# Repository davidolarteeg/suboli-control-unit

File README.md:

SUBOLI MK2 control unit — KiCad 10 project for design review.

Current procurement and missing-component tracker: `procurement/INVENTORY.md`.

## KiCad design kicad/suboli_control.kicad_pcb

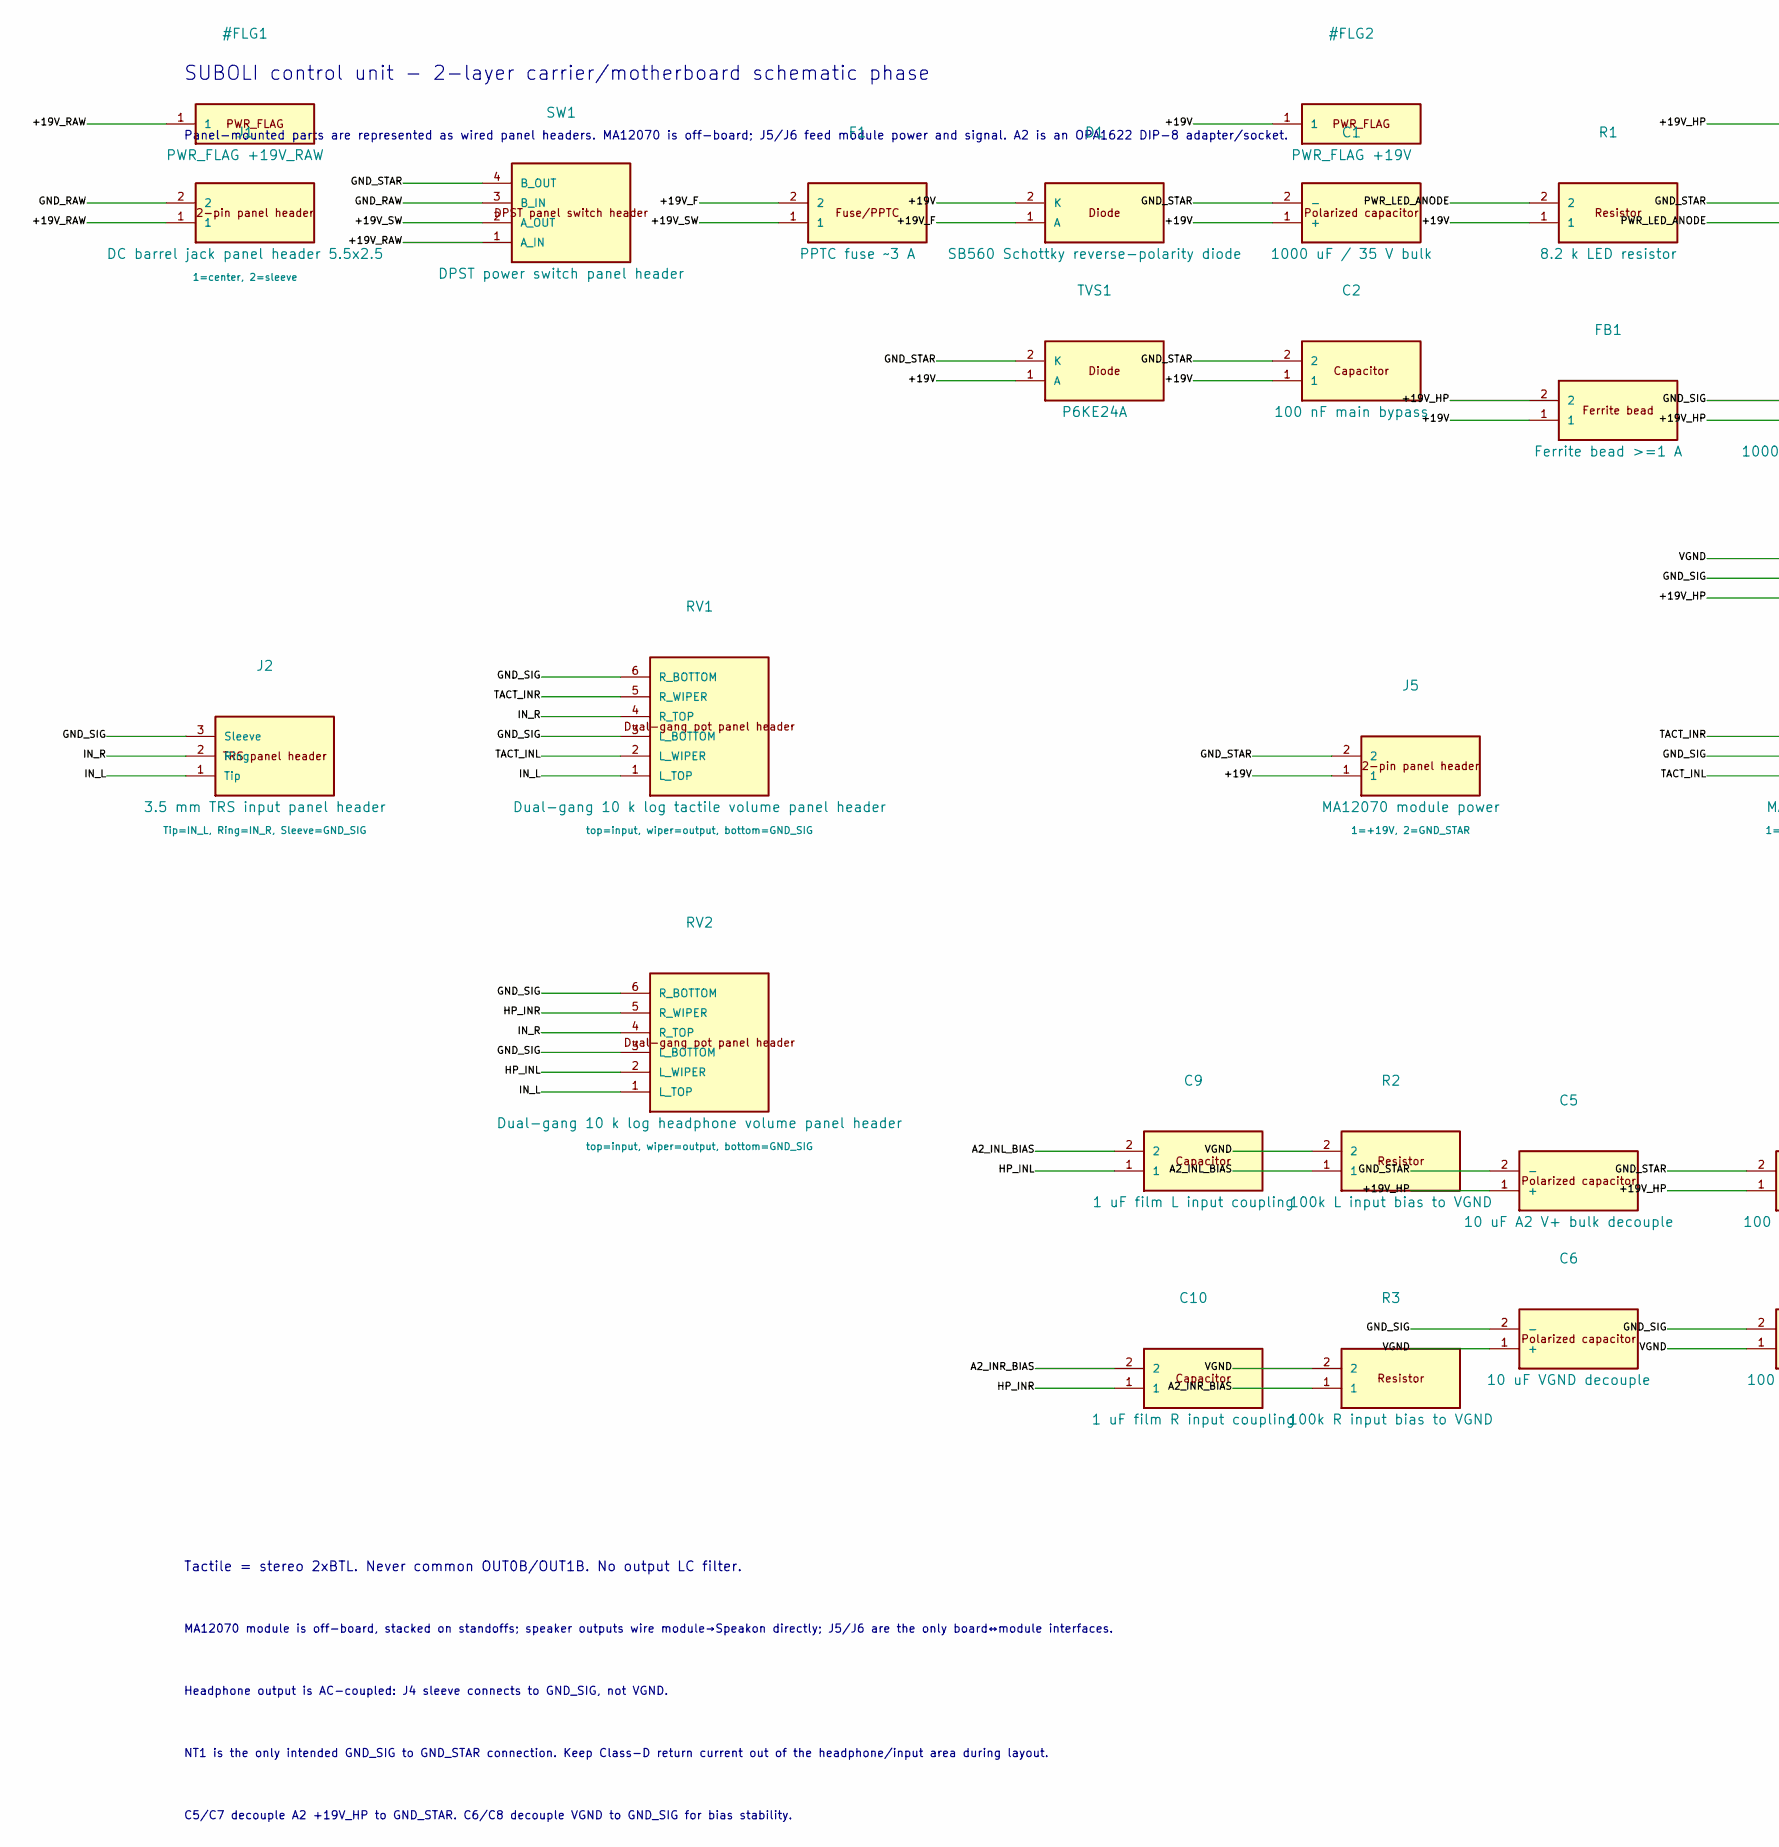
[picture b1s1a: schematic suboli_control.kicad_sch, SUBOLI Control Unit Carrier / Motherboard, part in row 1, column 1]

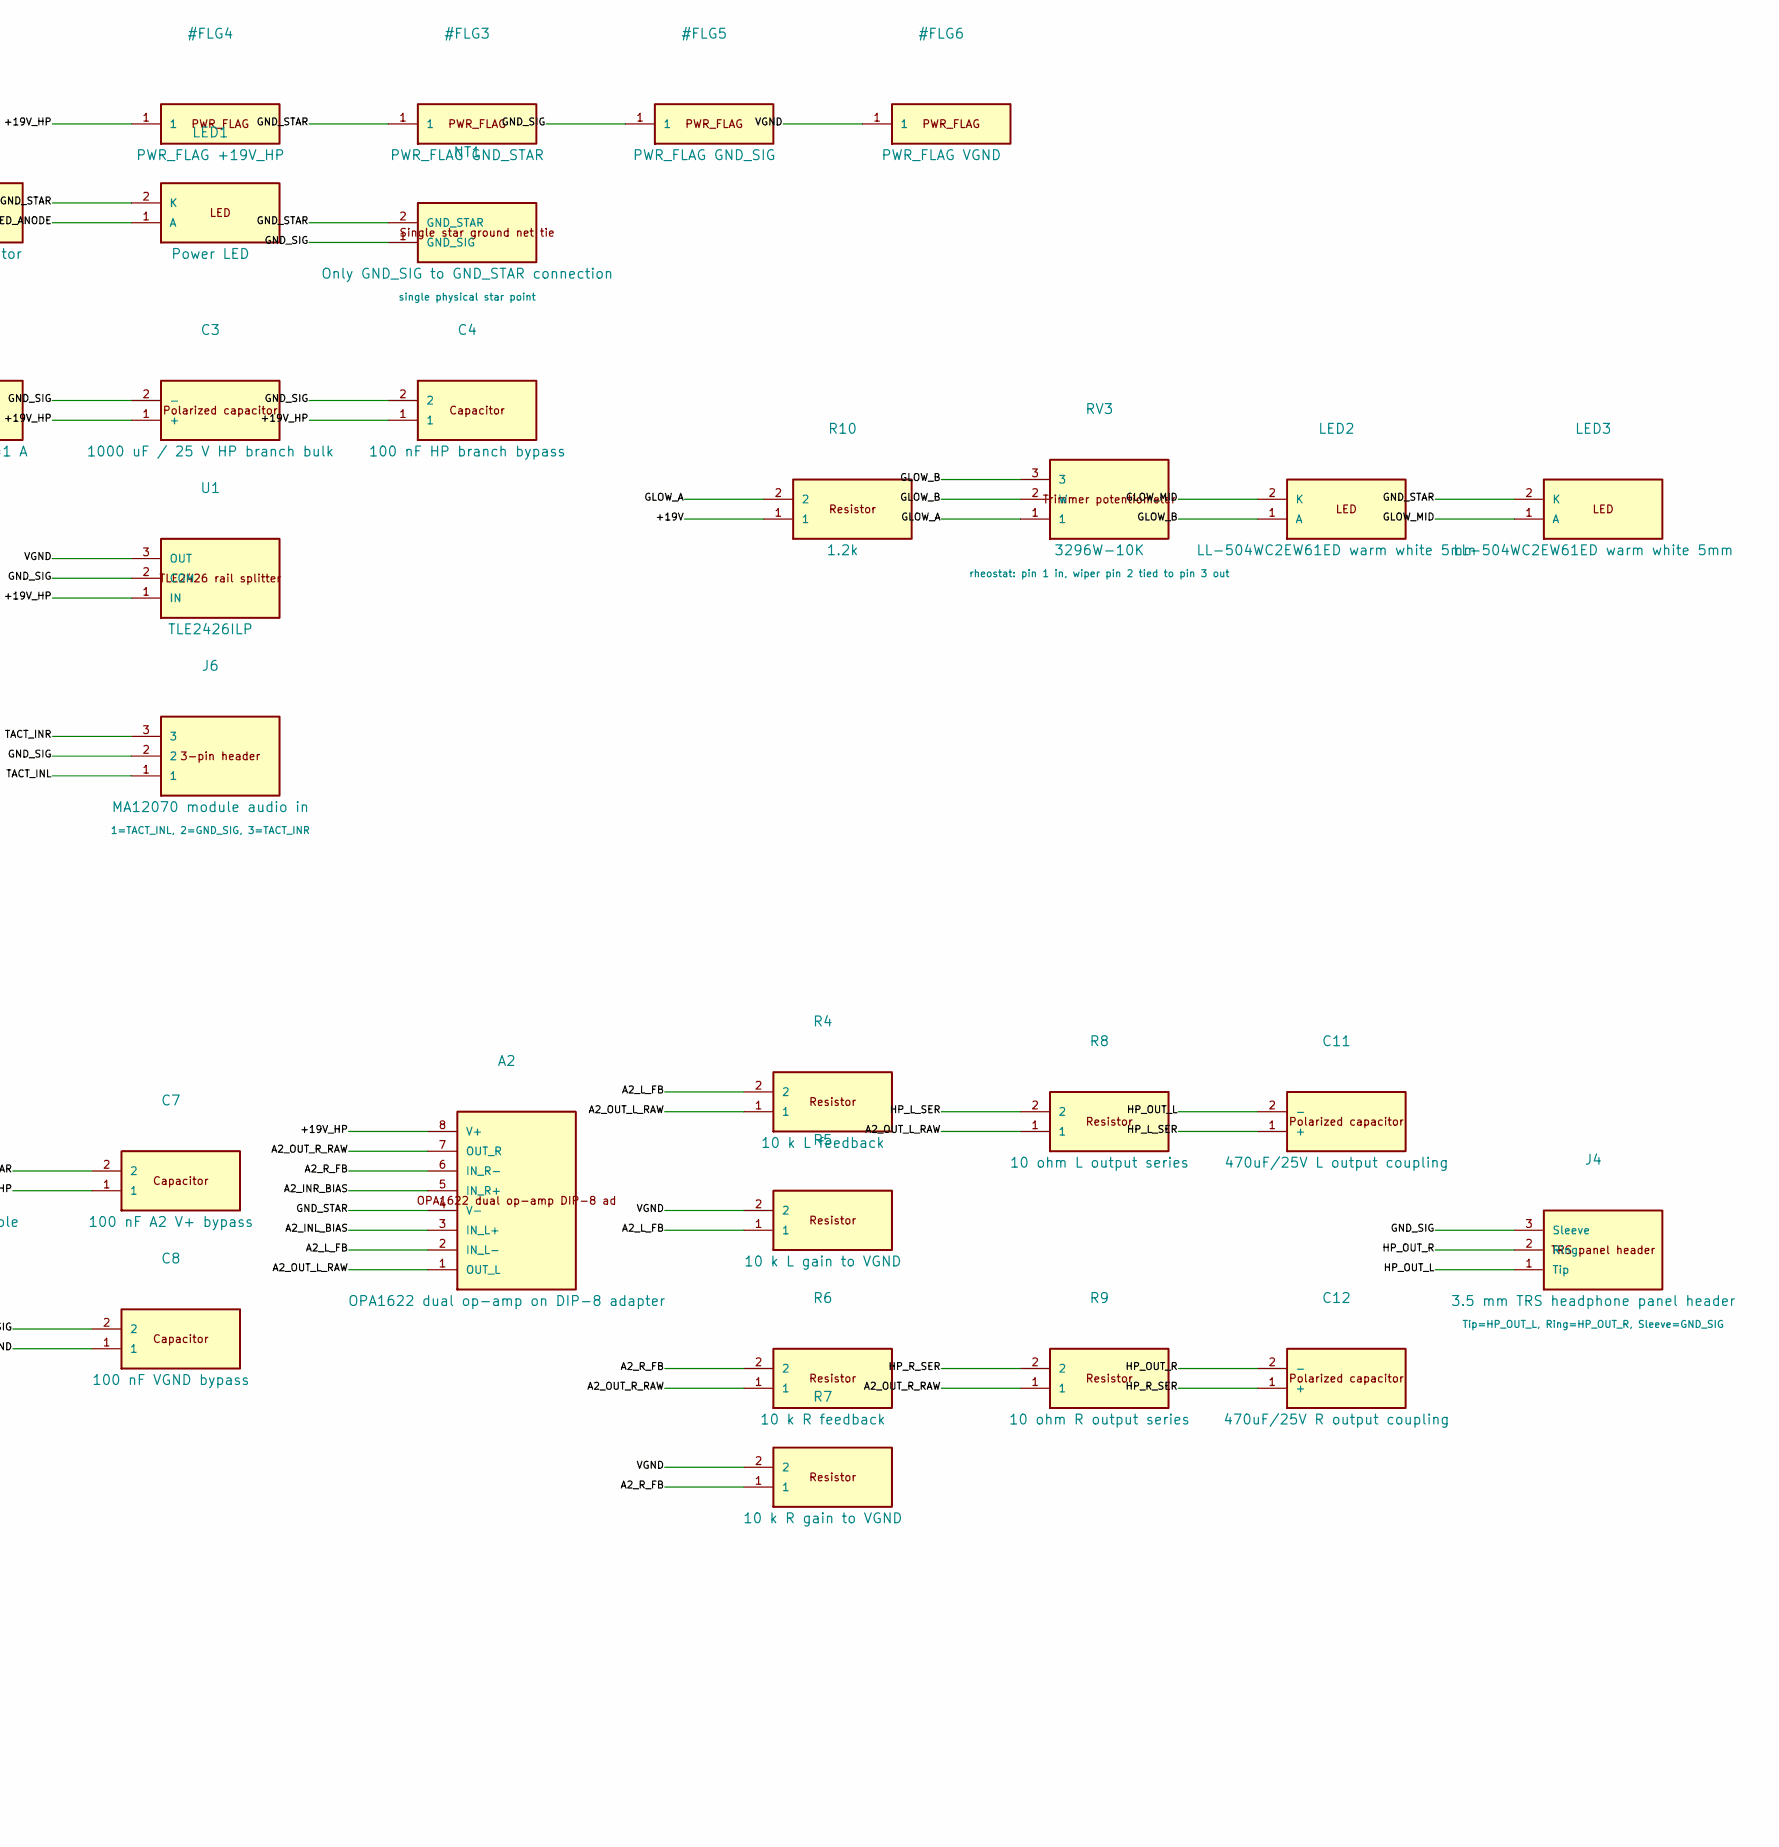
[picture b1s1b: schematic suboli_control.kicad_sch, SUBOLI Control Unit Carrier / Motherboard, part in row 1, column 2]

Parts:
A2: OPA1622 dual op-amp on DIP-8 adapter; DIP-8_W7.62mm_Socket
C1: 1000 uF / 35 V bulk; CP_Radial_D16.0mm_P7.50mm
C2: 100 nF main bypass; C_Disc_D7.5mm_W4.4mm_P5.00mm
C3: 1000 uF / 25 V HP branch bulk; CP_Radial_D10.0mm_P5.00mm
C4: 100 nF HP branch bypass; C_Disc_D7.5mm_W4.4mm_P5.00mm
C5: 10 uF A2 V+ bulk decouple; CP_Radial_D5.0mm_P2.00mm
C6: 10 uF VGND decouple; CP_Radial_D5.0mm_P2.00mm
C7: 100 nF A2 V+ bypass; C_Disc_D7.5mm_W4.4mm_P5.00mm
C8: 100 nF VGND bypass; C_Disc_D7.5mm_W4.4mm_P5.00mm
C9: 1 uF film L input coupling; C_Rect_L7.2mm_W4.5mm_P5.00mm
C10: 1 uF film R input coupling; C_Rect_L7.2mm_W4.5mm_P5.00mm
C11: 470uF/25V L output coupling; CP_Radial_D10.0mm_P5.00mm
C12: 470uF/25V R output coupling; CP_Radial_D10.0mm_P5.00mm
D1: SB560 Schottky reverse-polarity diode; D_DO-201AD_P15.24mm_Horizontal
F1: PPTC fuse ~3 A; PPTC_LP30-300_P7.60mm
FB1: Ferrite bead >=1 A; L_Axial_L12.0mm_D5.0mm_P15.24mm_Horizontal_Fastron_MISC
J1: DC barrel jack panel header 5.5x2.5; PhoenixContact_MSTBA_2,5_2-G-5,08_1x02_P5.08mm_Horizontal
J2: 3.5 mm TRS input panel header; JST_XH_B3B-XH-A_1x03_P2.50mm_Vertical
J4: 3.5 mm TRS headphone panel header; JST_XH_B3B-XH-A_1x03_P2.50mm_Vertical
J5: MA12070 module power; PhoenixContact_MSTBA_2,5_2-G-5,08_1x02_P5.08mm_Horizontal
J6: MA12070 module audio in; JST_XH_B3B-XH-A_1x03_P2.50mm_Vertical
LED1: Power LED; LED_D5.0mm
LED2, LED3: LL-504WC2EW61ED warm white 5mm; LED_D5.0mm
NT1: Only GND_SIG to GND_STAR connection; NetTie-2_SMD_Pad0.5mm
R1: 8.2 k LED resistor; R_Axial_DIN0207_L6.3mm_D2.5mm_P10.16mm_Horizontal
R2: 100k L input bias to VGND; R_Axial_DIN0207_L6.3mm_D2.5mm_P10.16mm_Horizontal
R3: 100k R input bias to VGND; R_Axial_DIN0207_L6.3mm_D2.5mm_P10.16mm_Horizontal
R4: 10 k L feedback; R_Axial_DIN0207_L6.3mm_D2.5mm_P10.16mm_Horizontal
R5: 10 k L gain to VGND; R_Axial_DIN0207_L6.3mm_D2.5mm_P10.16mm_Horizontal
R6: 10 k R feedback; R_Axial_DIN0207_L6.3mm_D2.5mm_P10.16mm_Horizontal
R7: 10 k R gain to VGND; R_Axial_DIN0207_L6.3mm_D2.5mm_P10.16mm_Horizontal
R8: 10 ohm L output series; R_Axial_DIN0207_L6.3mm_D2.5mm_P10.16mm_Horizontal
R9: 10 ohm R output series; R_Axial_DIN0207_L6.3mm_D2.5mm_P10.16mm_Horizontal
R10: 1.2k; R_Axial_DIN0207_L6.3mm_D2.5mm_P10.16mm_Horizontal
RV1: Dual-gang 10 k log tactile volume panel header; JST_XH_B6B-XH-A_1x06_P2.50mm_Vertical
RV2: Dual-gang 10 k log headphone volume panel header; JST_XH_B6B-XH-A_1x06_P2.50mm_Vertical
RV3: 3296W-10K; Potentiometer_Bourns_3296W_Vertical
SW1: DPST power switch panel header; PhoenixContact_MSTBA_2,5_4-G-5,08_1x04_P5.08mm_Horizontal
TVS1: P6KE24A; D_DO-15_P10.16mm_Horizontal
U1: TLE2426ILP; TO-92_Inline

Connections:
/+19V: C1.1 (+), C2.1, D1.2 (K), FB1.1, J5.1, R1.1, R10.1, TVS1.1 (A)
/+19V_F: D1.1 (A), F1.2
/+19V_HP: A2.8 (V+), C3.1 (+), C4.1, C5.1 (+), C7.1, FB1.2, U1.1 (IN)
/+19V_RAW: J1.1, SW1.1 (A_IN)
/+19V_SW: F1.1, SW1.2 (A_OUT)
/A2_INL_BIAS: A2.3 (IN_L+), C9.2, R2.1
/A2_INR_BIAS: A2.5 (IN_R+), C10.2, R3.1
/A2_L_FB: A2.2 (IN_L-), R4.2, R5.1
/A2_OUT_L_RAW: A2.1 (OUT_L), R4.1, R8.1
/A2_OUT_R_RAW: A2.7 (OUT_R), R6.1, R9.1
/A2_R_FB: A2.6 (IN_R-), R6.2, R7.1
/GLOW_A: R10.2, RV3.1
/GLOW_B: LED2.1 (A), RV3.2 (W), RV3.3
/GLOW_MID: LED2.2 (K), LED3.1 (A)
/GND_RAW: J1.2, SW1.3 (B_IN)
/GND_SIG: C3.2 (-), C4.2, C6.2 (-), C8.2, J2.3 (Sleeve), J4.3 (Sleeve), J6.2, NT1.1 (GND_SIG), RV1.3 (L_BOTTOM), RV1.6 (R_BOTTOM), RV2.3 (L_BOTTOM), RV2.6 (R_BOTTOM), U1.2 (COM)
/GND_STAR: A2.4 (V-), C1.2 (-), C2.2, C5.2 (-), C7.2, J5.2, LED1.2 (K), LED3.2 (K), NT1.2 (GND_STAR), SW1.4 (B_OUT), TVS1.2 (K)
/HP_INL: C9.1, RV2.2 (L_WIPER)
/HP_INR: C10.1, RV2.5 (R_WIPER)
/HP_L_SER: C11.1 (+), R8.2
/HP_OUT_L: C11.2 (-), J4.1 (Tip)
/HP_OUT_R: C12.2 (-), J4.2 (Ring)
/HP_R_SER: C12.1 (+), R9.2
/IN_L: J2.1 (Tip), RV1.1 (L_TOP), RV2.1 (L_TOP)
/IN_R: J2.2 (Ring), RV1.4 (R_TOP), RV2.4 (R_TOP)
/PWR_LED_ANODE: LED1.1 (A), R1.2
/TACT_INL: J6.1, RV1.2 (L_WIPER)
/TACT_INR: J6.3, RV1.5 (R_WIPER)
/VGND: C6.1 (+), C8.1, R2.2, R3.2, R5.2, R7.2, U1.3 (OUT)

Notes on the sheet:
SUBOLI control unit - 2-layer carrier/motherboard schematic phase
Panel-mounted parts are represented as wired panel headers. MA12070 is off-board; J5/J6 feed module power and signal. A2 is an OPA1622 DIP-8 adapter/socket.
Tactile = stereo 2xBTL. Never common OUT0B/OUT1B. No output LC filter.
MA12070 module is off-board, stacked on standoffs; speaker outputs wire module→Speakon directly; J5/J6 are the only board↔module interfaces.
Headphone output is AC-coupled: J4 sleeve connects to GND_SIG, not VGND.
NT1 is the only intended GND_SIG to GND_STAR connection. Keep Class-D return current out of the headphone/input area during layout.
C5/C7 decouple A2 +19V_HP to GND_STAR. C6/C8 decouple VGND to GND_SIG for bias stability.

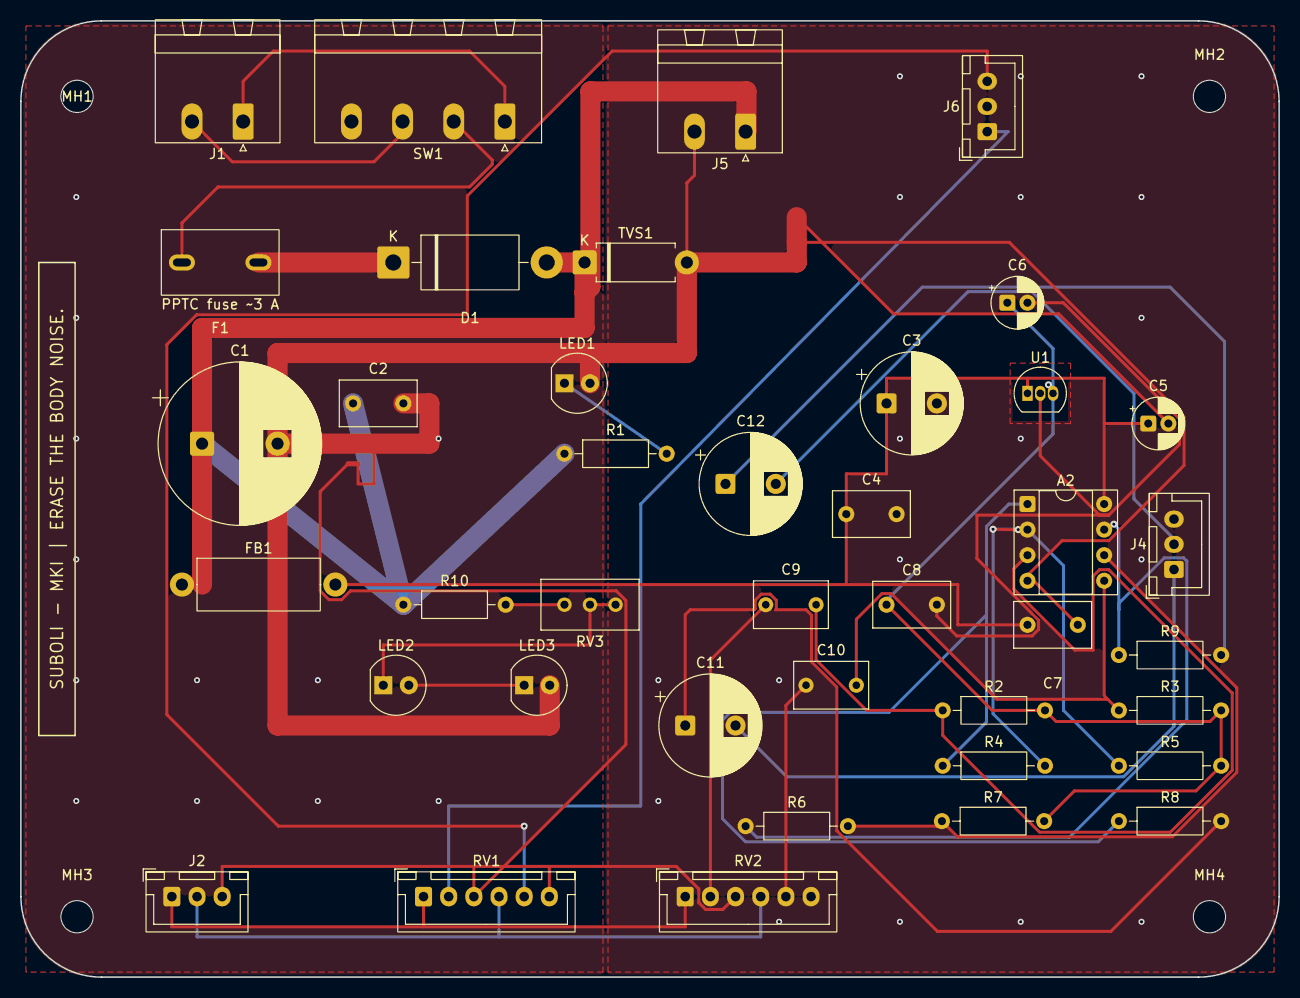
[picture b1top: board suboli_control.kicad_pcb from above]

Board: 2 copper layers, 125.0 x 95.0 mm, 45 parts (0 on the bottom side), 29 nets.

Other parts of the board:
MH1, MH2, MH3, MH4: MountingHole_3.2mm_M3

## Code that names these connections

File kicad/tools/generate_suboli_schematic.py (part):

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    Component("TVS1", "SMBJ20A TVS", "D_2PIN", 138, 54, {"1": "+19V", "2": "GND_STAR"}),
    Component("C1", "1000 uF / 35 V bulk", "CP_2PIN", 170, 34, {"1": "+19V", "2": "GND_STAR"}),
    Component("C2", "100 nF main bypass", "C_2PIN", 170, 54, {"1": "+19V", "2": "GND_STAR"}),
    Component("R1", "8.2 k LED resistor", "R_2PIN", 204, 34, {"1": "+19V", "2": "PWR_LED_ANODE"}),
    Component("LED1", "Power LED", "LED_2PIN", 236, 34, {"1": "PWR_LED_ANODE", "2": "GND_STAR"}),
    Component("FB1", "Ferrite bead >=1 A", "FERRITE_2PIN", 204, 58, {"1": "+19V", "2": "+19V_HP"}),
    Component("J2", "3.5 mm TRS input panel header", "CONN_3_TRS", 30, 104, {"1": "IN_L", "2": "IN_R", "3": "GND_SIG"}, fields={"Function": "3.5 mm TRS input jack", "Pinout": "Tip=IN_L, Ring=IN_R, Sleeve=GND_SIG"}),
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    Component("J3", "4-pole Speakon/XLR panel header", "CONN_4", 292, 104, {"1": "OUTL+", "2": "OUTL−", "3": "OUTR+", "4": "OUTR−"}, fields={"Function": "4-pole Speakon/XLR tactile output", "Pinout": "1+=OUTL+, 1-=OUTL−, 2+=OUTR+, 2-=OUTR−"}),
    Component("C3", "1000 uF / 25 V HP branch bulk", "CP_2PIN", 236, 58, {"1": "+19V_HP", "2": "GND_SIG"}),
    Component("C4", "100 nF HP branch bypass", "C_2PIN", 268, 58, {"1": "+19V_HP", "2": "GND_SIG"}),
    Component("U1", "TLE2426 rail splitter", "TLE2426_3PIN", 236, 82, {"1": "+19V_HP", "2": "GND_SIG", "3": "VGND"}, fields={"Function": "Virtual ground rail splitter"}),
    Component("C5", "10 uF A2 V+ bulk decouple", "CP_2PIN", 198, 158, {"1": "+19V_HP", "2": "GND_STAR"}),
    Component("C6", "10 uF VGND decouple", "CP_2PIN", 198, 178, {"1": "VGND", "2": "GND_SIG"}),
    Component("C7", "100 nF A2 V+ bypass", "C_2PIN", 230, 158, {"1": "+19V_HP", "2": "GND_STAR"}),
    Component("C8", "100 nF VGND bypass", "C_2PIN", 230, 178, {"1": "VGND", "2": "GND_SIG"}),
    Component("C9", "1 uF film L input coupling", "C_2PIN", 150, 156, {"1": "HP_INL", "2": "A2_INL_BIAS"}),
    Component("C10", "1 uF film R input coupling", "C_2PIN", 150, 184, {"1": "HP_INR", "2": "A2_INR_BIAS"}),
    Component("R2", "100k L input bias to VGND", "R_2PIN", 176, 156, {"1": "A2_INL_BIAS", "2": "VGND"}),
    Component("R3", "100k R input bias to VGND", "R_2PIN", 176, 184, {"1": "A2_INR_BIAS", "2": "VGND"}),
    Component("A2", "OPA1622 dual op-amp on DIP-8 adapter", "A2_OPA1622_DIP8", 274, 168, {"1": "A2_OUT_L_RAW", "2": "A2_L_FB", "3": "A2_INL_BIAS", "4": "GND_STAR", "5": "A2_INR_BIAS", "6": "A2_R_FB", "7": "A2_OUT_R_RAW", "8": "+19V_HP"}),
    Component("R4", "10 k L feedback", "R_2PIN", 316, 148, {"1": "A2_OUT_L_RAW", "2": "A2_L_FB"}),
    Component("R5", "10 k L gain to VGND", "R_2PIN", 316, 162, {"1": "A2_L_FB", "2": "VGND"}),
    Component("R6", "10 k R feedback", "R_2PIN", 316, 182, {"1": "A2_OUT_R_RAW", "2": "A2_R_FB"}),
    Component("R7", "10 k R gain to VGND", "R_2PIN", 316, 196, {"1": "A2_R_FB", "2": "VGND"}),
    Component("R8", "10 ohm L output series", "R_2PIN", 350, 150, {"1": "A2_OUT_L_RAW", "2": "HP_L_SER"}),
    Component("R9", "10 ohm R output series", "R_2PIN", 350, 184, {"1": "A2_OUT_R_RAW", "2": "HP_R_SER"}),
    Component("C11", "470uF/25V L output coupling", "CP_2PIN", 382, 150, {"1": "HP_L_SER", "2": "HP_OUT_L"}),
    Component("C12", "470uF/25V R output coupling", "CP_2PIN", 382, 184, {"1": "HP_R_SER", "2": "HP_OUT_R"}),
    Component("J4", "3.5 mm TRS headphone panel header", "CONN_3_TRS", 414, 168, {"1": "HP_OUT_L", "2": "HP_OUT_R", "3": "GND_SIG"}, fields={"Function": "3.5 mm TRS headphone output jack", "Pinout": "Tip=HP_OUT_L, Ring=HP_OUT_R, Sleeve=GND_SIG"}),
    Component("NT1", "Only GND_SIG to GND_STAR connection", "NET_TIE_2", 268, 36, {"1": "GND_SIG", "2": "GND_STAR"}, fields={"Purpose": "single physical star point"}),
    Component("#FLG1", "PWR_FLAG +19V_RAW", "PWR_FLAG_LOCAL", 28, 20, {"1": "+19V_RAW"}),
    Component("#FLG2", "PWR_FLAG +19V", "PWR_FLAG_LOCAL", 170, 20, {"1": "+19V"}),
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
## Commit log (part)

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2026-06-11 Initial review package: schematic, ERC, netlist, BOM, renders
2026-06-11 Review fixes R1: annotation, final values, TVS populated (SMBJ20A)
2026-06-11 R2: interior glow circuit, power-tracked via SW1
2026-06-11 R3: footprints locked from verified parts, TVS=P6KE24A, script archived
2026-06-11 R3.1: correct 3 footprint library names (MSTB pluggable lib, Fastron suffix)
2026-06-11 R4: MA12070 off-board (stacked), J3+OUT nets removed, J5/J6 added
2026-06-13 R5: BOM enrichment + C1 footprint fix + design rulebook + PCB capability report
2026-06-13 R5.1: skip design rulebook task
2026-06-14 Add locked SUBOLI design rulebook (repo-authored, verified)
2026-06-14 Add SUBOLI manufacturing export scripts
2026-06-14 Remove generated Python bytecode from design scripts
2026-06-15 R6: initial PCB placement (41 parts, outline, mounting holes)
2026-06-15 R7: net classes (Power 2.0mm / Default 0.3mm) with net assignments
2026-06-15 R8: attempt auto-route of power + ground + glow nets
2026-06-15 R8.1: fix glow trimmer short
2026-06-15 R9: DRC clean - silkscreen + TO-92 mask fixes, 0 violations
2026-06-15 R10: ground pour zones (GND_STAR left / GND_SIG right, split at x70)
2026-06-15 R11: route power leftover branches on B.Cu under ground pour
2026-06-16 R12: route input + tactile signal nets
2026-06-16 R13: hand-routed analog cluster - board fully routed, 0 DRC, 0 unconnected
2026-06-16 R14: ground stitching vias
2026-06-16 R15: Flag 3 clearance fix - HP_L_SER spacing, board final 0/0
2026-06-16 R16: manufacturing export - Gerbers, drill, centroid, BOM
2026-06-16 R17: BOM MPN backfill
2026-06-17 R18: rounded board corners (5mm fillets)
2026-06-17 R19: rounded Gerbers + restored R17 BOM
2026-06-17 R20: 8mm corner radius + re-export Gerbers + restore BOM
2026-06-17 R21: rotate J1/SW1/J5 180deg + relocate MH1 + clear connector traces for reroute
2026-06-17 R22: fix J1/SW1 placement clear of MH1 + reroute
2026-06-18 R23-wip: moved connectors + reconnected (16 DRC to resolve)
2026-06-18 R23: resolve real DRC after connector moves
2026-06-18 R24: re-export Gerbers (final board with fixed connectors)
2026-06-20 Add KiCad geometry extractor
2026-06-30 Add SUBOLI procurement inventory tracker
2026-06-30 Add supply tracker dashboard
    Interactive single-file HTML procurement tracker covering all 53 line items across 9 suppliers. Dual-currency (EUR + HUF), delivery method/carrier/ETA per order, clickable status cycling, open-items 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
